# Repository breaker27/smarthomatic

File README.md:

smarthomatic
============

smarthomatic (SHC) is an **open source home automation system**
providing a framework for building up a bigger network of sensors and
actuators that all work together. It consists of several completely
developed hardware devices you can build up yourself and the software
running on those devices.

This project **concentrates on the hardware devices** and their software
(firmware), not on end user interfaces for control tasks like web
interfaces or smartphone apps. Nonetheless this system is designed to be
easily integrated in such systems.

For more information, visit the website at
http://www.smarthomatic.org.

License Information Hardware Files
----------------------------------

All **hardware** files (schematics and layout) are stored under the
"hardware" subdirectory and are copyright (c) 2013 Uwe Freese, licensed
under the Creative Commons Attribution-ShareAlike 3.0 Unported:
(CC BY-SA 3.0): http://creativecommons.org/licenses/by-sa/3.0/deed.en.

License Information Software
----------------------------

All files not in the hardware subdirectory belong to the software (device
firmware, control software or tools).

The smarthomatic **software** is free software: you can redistribute
it and/or modify it under the terms of the GNU General Public License as
published by the Free Software Foundation, either version 3 of the
License, or (at your option) any later version.

smarthomatic is distributed in the hope that it will be useful, but
WITHOUT ANY WARRANTY; without even the implied warranty of
MERCHANTABILITY or FITNESS FOR A PARTICULAR PURPOSE. See the GNU General
Public License for more details.

You should have received a copy of the GNU General Public License along
with smarthomatic. If not, see <http://www.gnu.org/licenses/>.

License Information Logo
------------------------

The smarthomatic logo ("House") and logotype, also used in the hardware
layouts, are copyrighted (c) by 2013 by Uwe Freese.

The logo and logotype may be used on hardware (boards or devices) or
description of those only for private purposes for devices included in
the project repository and which are therefore available to the public.
For derived or modified versions, devices not existing in the repository,
completely different products or for commercial boards or devices or to
describe them, the logo must not be used without explicit permission from
Uwe Freese.

For more information on using the logo or logotype outside the hardware
layouts, please read the legal info on the website
http://www.smarthomatic.org.

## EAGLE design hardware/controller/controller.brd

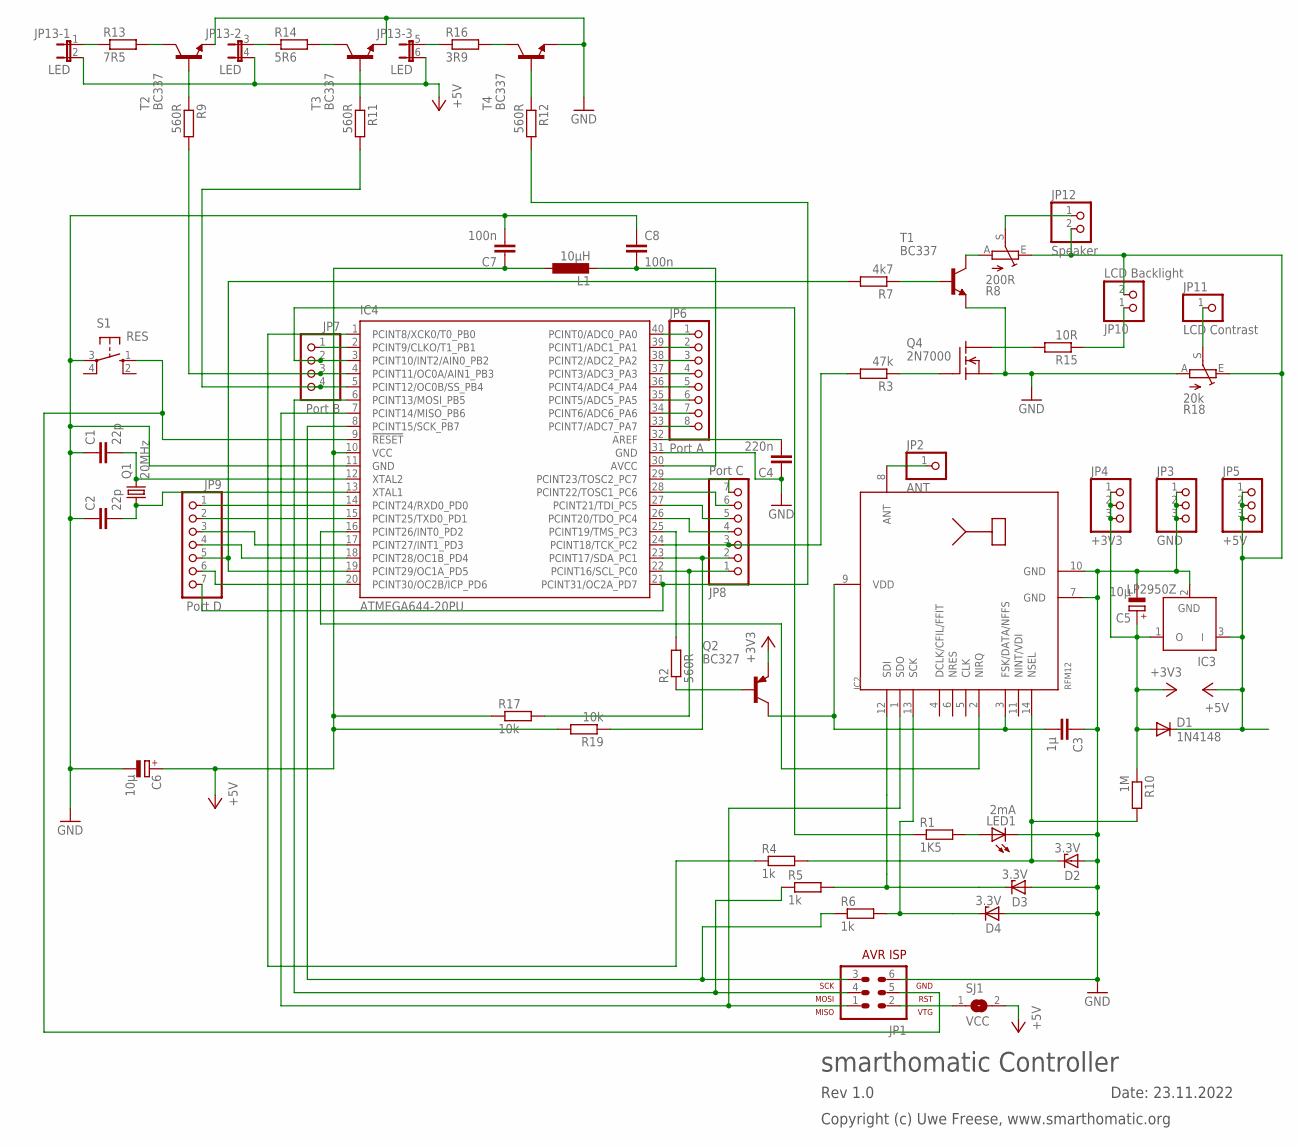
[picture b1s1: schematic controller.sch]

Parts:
C1, C2: 22p; C025-024X044
C3: 1µ; C025-030X050
C4: 220n; C025-030X050
C5, C6: 10µ; E1,8-4
C7, C8: 100n; C050-024X044
D1: 1N4148; DO35-7
D2, D3, D4: 3.3V; ZDIO-5
IC2: RFM12; RFM
IC3: LP2950Z; TO92
IC4: ATMEGA644-20PU; DIL40
JP1: AVR-ISP-6
JP2: ANT; 1X01
JP3: GND; 1X03
JP4: +3V3; 1X03
JP5: +5V; 1X03
JP6: Port A; 1X08
JP7: Port B; 1X04
JP8: Port C; 1X07
JP9: Port D; 1X07
JP10: LCD Backlight; 1X02
JP11: LCD Contrast; 1X01
JP12: Speaker; 1X02
JP13: LED; JP3Q
L1: 10µH; 0207/10
LED1: 2mA; LED3MM
Q1: 20MHz; HC49/S
Q2: BC327; TO92
Q4: 2N7000; TO-92
R1: 1K5; 0207/7
R2, R9, R11, R12: 560R; 0207/7
R3: 47k; 0207/7
R4, R5, R6: 1k; 0207/7
R7: 4k7; 0207/7
R8: 200R; CA9H
R10: 1M; 0207/7
R13: 7R5; 0207/7
R14: 5R6; 0207/7
R15: 10R; 0207/7
R16: 3R9; 0207/7
R17, R19: 10k; 0207/7
R18: 20k; CA9H
S1: RES; B3F-10XX
SJ1: VCC; SJ
T1, T2, T3, T4: BC337; TO92

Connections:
+3V3: C5.+, D1.A, IC3.1 (O), JP4.1, JP4.2, JP4.3, Q2.1 (E), R10.1
+5V: C6.+, C7.1, D1.C, IC3.3 (I), IC4.10 (VCC), JP5.1, JP5.2, JP5.3, JP10.2, JP12.2, JP13.2, JP13.4 (2), JP13.6 (2), L1.1, R8.E, R17.1, R18.E, R19.2, SJ1.2
GND: C1.1, C2.1, C3.1, C4.1, C5.-, C6.-, C7.2, C8.1, D2.A, D3.A, D4.A, IC2.7 (GND), IC2.10 (GND), IC3.2 (GND), IC4.11 (GND), IC4.31 (GND), JP1.6, JP3.1, JP3.2, JP3.3, LED1.K (C), Q4.1 (S), R18.A, S1.3, T1.1 (E), T2.1 (E), T3.1 (E), T4.1 (E)
unnamed: C1.2, IC4.12 (XTAL2), Q1.2
unnamed: C2.2, IC4.13 (XTAL1), Q1.1
unnamed: IC4.6 (PCINT13/MOSI_PB5), JP1.4, R5.1
unnamed: IC2.1 (SDO), IC4.7 (PCINT14/MISO_PB6), JP1.1
unnamed: D4.C, IC2.13 (SCK), R6.2
unnamed: C4.2, IC4.32 (AREF)
unnamed: IC4.8 (PCINT15/SCK_PB7), JP1.3, R6.1
unnamed: IC4.9 (!RESET), JP1.5, S1.1 (S)
unnamed: IC4.2 (PCINT9/CLKO/T1_PB1), JP7.1
unnamed: IC4.40 (PCINT0/ADC0_PA0), JP6.1
unnamed: IC4.39 (PCINT1/ADC1_PA1), JP6.2
unnamed: LED1.A, R1.2
unnamed: IC4.26 (PCINT20/TDO_PC4), JP8.4
unnamed: IC4.38 (PCINT2/ADC2_PA2), JP6.3
unnamed: IC2.2 (NIRQ), IC4.16 (PCINT26/INT0_PD2)
unnamed: D3.C, IC2.12 (SDI), R5.2
unnamed: IC4.37 (PCINT3/ADC3_PA3), JP6.4
unnamed: JP1.2, SJ1.1
unnamed: IC4.36 (PCINT4/ADC4_PA4), JP6.5
unnamed: IC4.35 (PCINT5/ADC5_PA5), JP6.6
unnamed: IC4.29 (PCINT23/TOSC2_PC7), JP8.7
unnamed: IC4.34 (PCINT6/ADC6_PA6), JP6.7
unnamed: IC4.33 (PCINT7/ADC7_PA7), JP6.8
unnamed: IC4.3 (PCINT10/INT2/AIN0_PB2), JP7.2, R1.1
unnamed: IC2.8 (ANT), JP2.1
unnamed: IC4.1 (PCINT8/XCK0/T0_PB0), R4.1
unnamed: D2.C, IC2.14 (NSEL), R4.2, R10.2
unnamed: IC4.25 (PCINT19/TMS_PC3), R2.2
unnamed: Q2.2 (B), R2.1
unnamed: IC4.4 (PCINT11/OC0A/AIN1_PB3), JP7.3, R9.2
unnamed: IC4.5 (PCINT12/OC0B/SS_PB4), JP7.4, R11.2
unnamed: C3.2, IC2.3 (FSK/DATA/NFFS), IC2.9 (VDD), Q2.3 (C)
unnamed: IC4.22 (PCINT16/SCL_PC0), JP8.1, R17.2
unnamed: IC4.23 (PCINT17/SDA_PC1), JP8.2, R19.1
unnamed: IC4.24 (PCINT18/TCK_PC2), JP8.3, R3.2
unnamed: IC4.19 (PCINT29/OC1A_PD5), JP9.5, R7.2
unnamed: IC4.28 (PCINT22/TOSC1_PC6), JP8.6
unnamed: IC4.20 (PCINT30/OC2B/ICP_PD6), JP9.6
unnamed: IC4.14 (PCINT24/RXD0_PD0), JP9.1
unnamed: IC4.15 (PCINT25/TXD0_PD1), JP9.2
unnamed: IC4.17 (PCINT27/INT1_PD3), JP9.3
unnamed: IC4.18 (PCINT28/OC1B_PD4), JP9.4
unnamed: IC4.21 (PCINT31/OC2A_PD7), JP9.7, R12.2
unnamed: IC4.27 (PCINT21/TDI_PC5), JP8.5
unnamed: C8.2, IC4.30 (AVCC), L1.2
unnamed: R7.1, T1.2 (B)
unnamed: R8.A, T1.3 (C)
unnamed: JP12.1, R8.S
unnamed: Q4.2 (G), R3.1
unnamed: Q4.3 (D), R15.2
unnamed: JP10.1, R15.1
unnamed: JP11.1, R18.S
unnamed: R9.1, T2.2 (B)
unnamed: R11.1, T3.2 (B)
unnamed: R12.1, T4.2 (B)
unnamed: JP13.1, R13.1
unnamed: R13.2, T2.3 (C)
unnamed: JP13.3 (1), R14.1
unnamed: R14.2, T3.3 (C)
unnamed: JP13.5 (1), R16.1
unnamed: R16.2, T4.3 (C)

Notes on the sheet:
smarthomatic Controller
Date: 23.11.2022
Rev 1.0
Copyright (c) Uwe Freese, www.smarthomatic.org

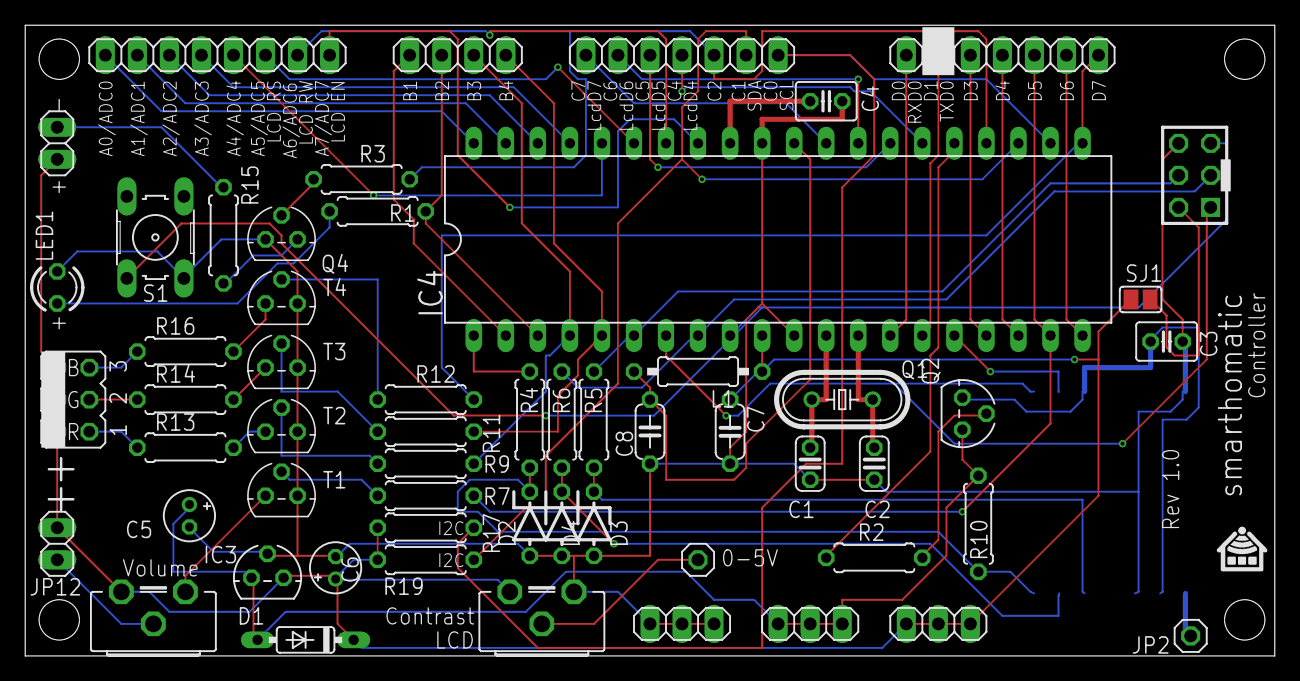
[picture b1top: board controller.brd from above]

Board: 2 copper layers, 99.1 x 50.0 mm, 58 parts (1 on the bottom side), 64 nets.

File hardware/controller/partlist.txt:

Partlist

Exported from controller.sch at 24.11.2022 18:18:30

EAGLE Version 7.1.0 Copyright (c) 1988-2014 CadSoft

Assembly variant: 

Part     Value          Device          Package      Library        Sheet

C1       22p            C-EU025-024X044 C025-024X044 rcl            1
C2       22p            C-EU025-024X044 C025-024X044 rcl            1
C3       1µ             C-EU025-030X050 C025-030X050 rcl            1
C4       220n           C-EU025-030X050 C025-030X050 rcl            1
C5       10µ            CPOL-EUE1.8-4   E1,8-4       rcl            1
C6       10µ            CPOL-EUE1.8-4   E1,8-4       rcl            1
C7       100n           C-EU050-024X044 C050-024X044 rcl            1
C8       100n           C-EU050-024X044 C050-024X044 rcl            1
D1       1N4148         1N4148DO35-7    DO35-7       diode          1
D2       3.3V           ZENER-DIODEZD-5 ZDIO-5       diode          1
D3       3.3V           ZENER-DIODEZD-5 ZDIO-5       diode          1
D4       3.3V           ZENER-DIODEZD-5 ZDIO-5       diode          1
IC2      RFM12          RFM12           RFM          hopeRF         1
IC3      LP2950Z        LP2950Z         TO92         linear         1
IC4      ATMEGA644-20PU ATMEGA644-20PU  DIL40        atmel          1
JP1      AVR-ISP-6      AVR-ISP-6       AVR-ISP-6    avr-5-4.16     1
JP2      ANT            PINHD-1X1       1X01         pinhead        1
JP3      GND            PINHD-1X3       1X03         pinhead        1
JP4      +3V3           PINHD-1X3       1X03         pinhead        1
JP5      +5V            PINHD-1X3       1X03         pinhead        1
JP6      Port A         PINHD-1X8       1X08         pinhead        1
JP7      Port B         PINHD-1X4       1X04         pinhead        1
JP8      Port C         PINHD-1X7       1X07         pinhead        1
JP9      Port D         PINHD-1X7       1X07         pinhead        1
JP10     LCD Backlight  PINHD-1X2       1X02         pinhead        1
JP11     LCD Contrast   PINHD-1X1       1X01         pinhead        1
JP12     Speaker        PINHD-1X2       1X02         pinhead        1
JP13     LED            JP3QE           JP3Q         jumper         1
L1       10µH           L-EU0207/10     0207/10      rcl            1
LED1     2mA            LED3MM          LED3MM       led            1
Q1       20MHz          CRYSTALHC49S    HC49/S       crystal        1
Q2       BC327          BC327           TO92         transistor-pnp 1
Q4       2N7000         TN0602N3        TO-92        transistor-fet 1
R1       1K5            R-EU_0207/7     0207/7       rcl            1
R2       560R           R-EU_0207/7     0207/7       rcl            1
R3       47k            R-EU_0207/7     0207/7       rcl            1
R4       1k             R-EU_0207/7     0207/7       rcl            1
R5       1k             R-EU_0207/7     0207/7       rcl            1
R6       1k             R-EU_0207/7     0207/7       rcl            1
R7       4k7            R-EU_0207/7     0207/7       rcl            1
R8       200R           TRIM_EU-CA9H    CA9H         pot            1
R9       560R           R-EU_0207/7     0207/7       rcl            1
R10      1M             R-EU_0207/7     0207/7       rcl            1
R11      560R           R-EU_0207/7     0207/7       rcl            1
R12      560R           R-EU_0207/7     0207/7       rcl            1
R13      7R5            R-EU_0207/7     0207/7       rcl            1
R14      5R6            R-EU_0207/7     0207/7       rcl            1
R15      10R            R-EU_0207/7     0207/7       rcl            1
R16      3R9            R-EU_0207/7     0207/7       rcl            1
R17      10k            R-EU_0207/7     0207/7       rcl            1
R18      20k            TRIM_EU-CA9H    CA9H         pot            1
R19      10k            R-EU_0207/7     0207/7       rcl            1
S1       RES            10-XX           B3F-10XX     switch-omron   1
SJ1      VCC            SJ              SJ           jumper         1
T1       BC337          BC337           TO92         transistor     1
T2       BC337          BC337           TO92         transistor     1
T3       BC337          BC337           TO92         transistor     1
T4       BC337          BC337           TO92         transistor     1

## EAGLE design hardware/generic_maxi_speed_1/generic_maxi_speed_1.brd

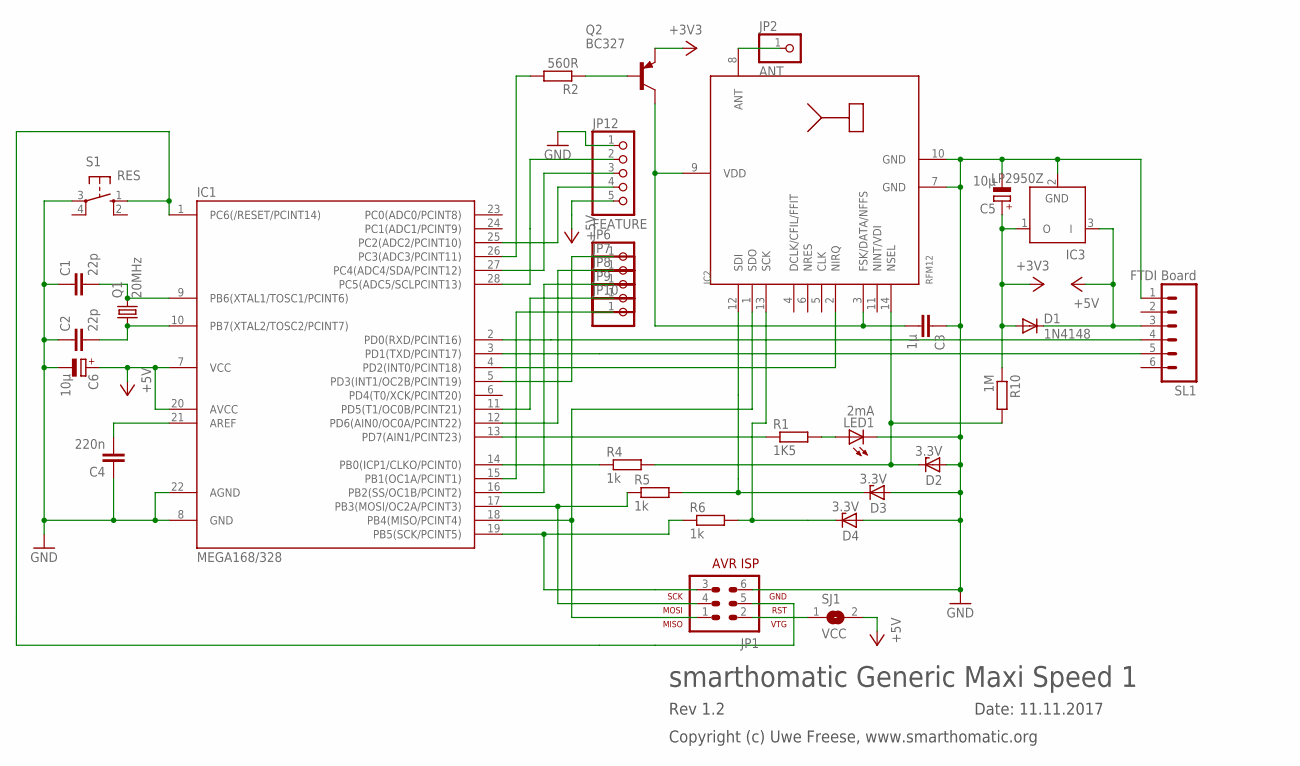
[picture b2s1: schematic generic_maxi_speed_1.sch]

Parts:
C1, C2: 22p; C025-024X044
C3: 1µ; C025-030X050
C4: 220n; C025-030X050
C5, C6: 10µ; E1,8-4
D1: 1N4148; DO35-7
D2, D3, D4: 3.3V; ZDIO-5
IC1: MEGA168/328; DIL28-3
IC2: RFM12; RFM
IC3: LP2950Z; TO92
JP1: AVR-ISP-6
JP2: ANT; 1X01
JP6, JP7, JP8, JP9, JP10: PINHD-1X1; 1X01
JP12: FEATURE; 1X05
LED1: 2mA; LED3MM
Q1: 20MHz; HC49/S
Q2: BC327; TO92
R1: 1K5; 0207/7
R2: 560R; 0207/7
R4, R5, R6: 1k; 0207/7
R10: 1M; 0207/7
S1: RES; B3F-10XX
SJ1: VCC; SJ
SL1: FTDI Board; 06P

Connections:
+3V3: C5.+, D1.A, IC3.1 (O), Q2.1 (E), R10.1
+5V: C6.+, D1.C, IC1.7 (VCC), IC1.20 (AVCC), IC3.3 (I), JP12.5, SJ1.2, SL1.3
GND: C1.1, C2.1, C3.1, C4.1, C5.-, C6.-, D2.A, D3.A, D4.A, IC1.8 (GND), IC1.22 (AGND), IC2.7 (GND), IC2.10 (GND), IC3.2 (GND), JP1.6, JP12.1, LED1.K (C), S1.3, SL1.1
unnamed: C1.2, IC1.9 (PB6(XTAL1/TOSC1/PCINT6)), Q1.2
unnamed: C2.2, IC1.10 (PB7(XTAL2/TOSC2/PCINT7)), Q1.1
unnamed: IC1.17 (PB3(MOSI/OC2A/PCINT3)), JP1.4, R5.1
unnamed: IC1.18 (PB4(MISO/PCINT4)), IC2.1 (SDO), JP1.1
unnamed: D4.C, IC2.13 (SCK), R6.2
unnamed: IC1.28 (PC5(ADC5/SCLPCINT13)), JP12.2
unnamed: IC1.19 (PB5(SCK/PCINT5)), JP1.3, R6.1
unnamed: IC1.1 (PC6(/RESET/PCINT14)), JP1.5, S1.1 (S)
unnamed: IC1.3 (PD1(TXD/PCINT17)), SL1.5
unnamed: IC1.2 (PD0(RXD/PCINT16)), SL1.4
unnamed: IC1.27 (PC4(ADC4/SDA/PCINT12)), JP12.3
unnamed: LED1.A, R1.2
unnamed: IC1.25 (PC2(ADC2/PCINT10)), JP12.4
unnamed: IC1.4 (PD2(INT0/PCINT18)), IC2.2 (NIRQ)
unnamed: D3.C, IC2.12 (SDI), R5.2
unnamed: IC1.5 (PD3(INT1/OC2B/PCINT19)), JP6.1
unnamed: JP1.2, SJ1.1
unnamed: IC1.11 (PD5(T1/OC0B/PCINT21)), JP9.1
unnamed: IC1.12 (PD6(AIN0/OC0A/PCINT22)), JP7.1
unnamed: IC1.13 (PD7(AIN1/PCINT23)), R1.1
unnamed: IC1.15 (PB1(OC1A/PCINT1)), JP10.1
unnamed: IC1.16 (PB2(SS/OC1B/PCINT2)), JP8.1
unnamed: C4.2, IC1.21 (AREF)
unnamed: IC2.8 (ANT), JP2.1
unnamed: IC1.14 (PB0(ICP1/CLKO/PCINT0)), R4.1
unnamed: D2.C, IC2.14 (NSEL), R4.2, R10.2
unnamed: IC1.26 (PC3(ADC3/PCINT11)), R2.2
unnamed: Q2.2 (B), R2.1
unnamed: C3.2, IC2.3 (FSK/DATA/NFFS), IC2.9 (VDD), Q2.3 (C)

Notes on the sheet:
smarthomatic Generic Maxi Speed 1
Date: 11.11.2017
Rev 1.2
Copyright (c) Uwe Freese, www.smarthomatic.org

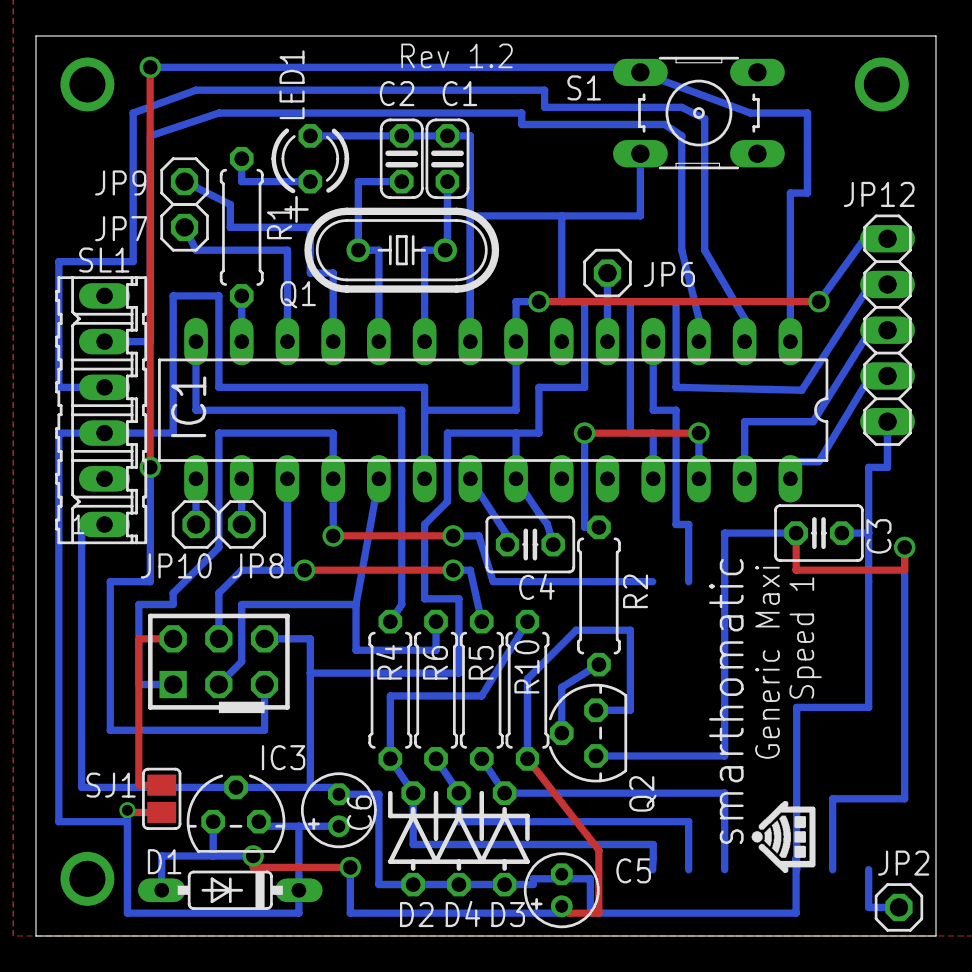
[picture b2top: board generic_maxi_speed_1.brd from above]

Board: 2 copper layers, 50.0 x 50.0 mm, 33 parts (1 on the bottom side), 32 nets.

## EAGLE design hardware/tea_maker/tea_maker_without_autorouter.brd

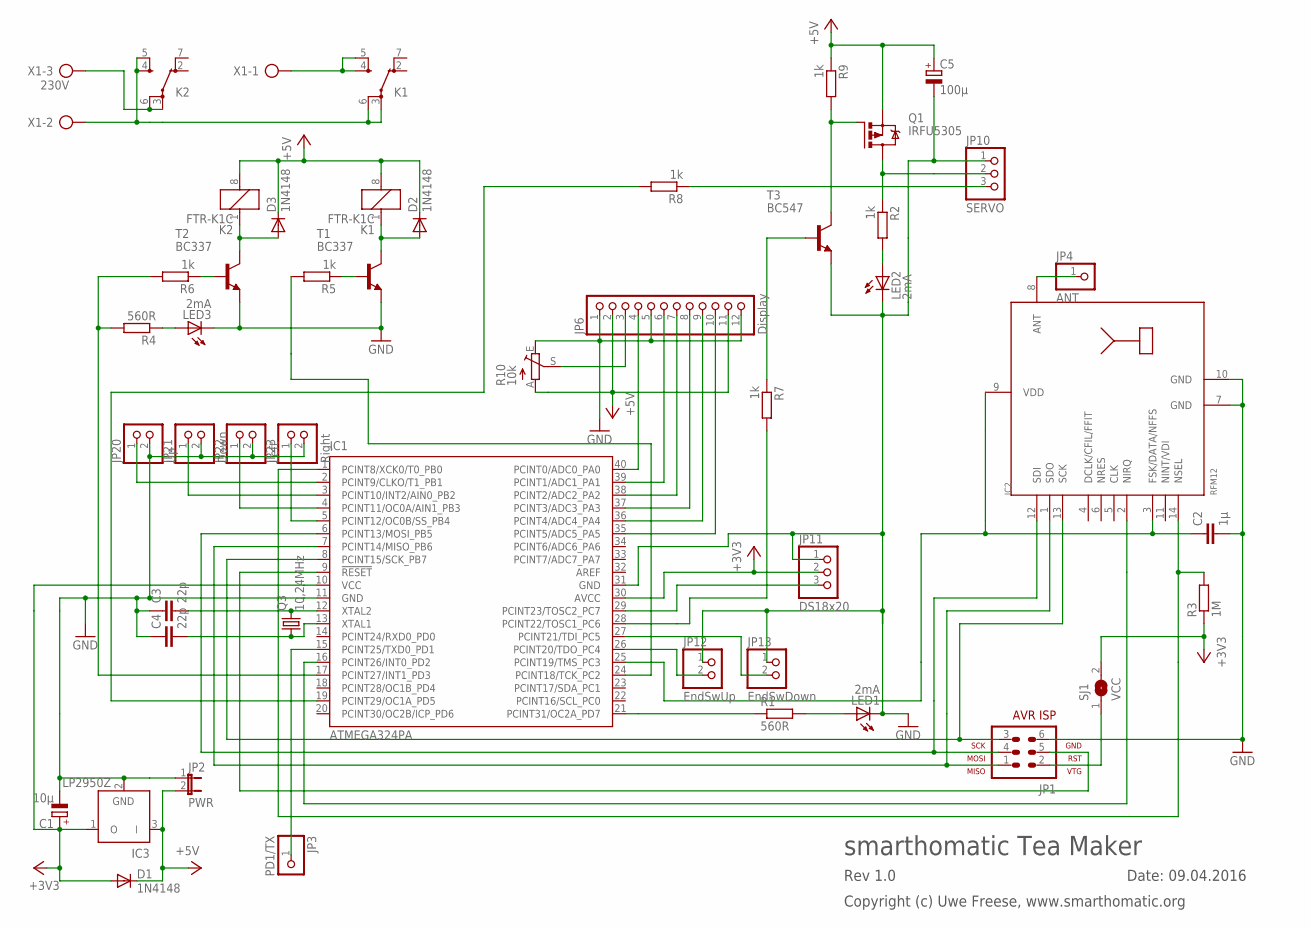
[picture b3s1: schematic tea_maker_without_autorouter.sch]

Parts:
C1: 10µ; E1,8-4
C2: 1µ; C5B3.5
C3, C4: 22p; C025-024X044
C5: 100µ; E2,5-7
D1, D2, D3: 1N4148; DO35-7
IC1: ATMEGA324PA; DIL40
IC2: RFM12; RFM
IC3: LP2950Z; TO92
JP1: AVR-ISP-6
JP2: PWR; JP1
JP3: PD1/TX; 1X01
JP4: ANT; 1X01
JP6: Display; 1X12
JP10: SERVO; 1X03
JP11: DS18x20; 1X03
JP12: EndSwUp; 1X02
JP13: EndSwDown; 1X02
JP20: Up; 1X02
JP21: Down; 1X02
JP22: Left; 1X02
JP23: Right; 1X02
K1, K2: FTR-K1C
LED1, LED2, LED3: 2mA; LED3MM
Q1: IRFU5305; I-PAK_TO251AA
Q3: 10,24MHz; HC49/S
R1, R4: 560R; 0207/7
R2, R5, R6, R7, R8, R9: 1k; 0207/7
R3: 1M; 0207/7
R10: 10k; PT-10S
SJ1: VCC; SJ
T1, T2: BC337; TO92
T3: BC547; TO92
X1: 230V; AK500/3

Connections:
+3V3: C1.+, D1.A, IC1.10 (VCC), IC1.30 (AVCC), IC3.1 (O), JP11.2, R3.1, SJ1.2
+5V: C5.+, D1.C, D2.C, D3.C, IC3.3 (I), JP2.2, JP6.2, JP6.11, K1.8 (2), K2.8 (2), Q1.3 (S), R9.1, R10.A
GND: C1.-, C2.2, C3.1, C4.1, C5.-, IC1.11 (GND), IC1.31 (GND), IC2.7 (GND), IC2.10 (GND), IC3.2 (GND), JP1.6, JP2.1, JP6.1, JP6.5, JP6.12, JP10.1, JP11.1, JP12.1, JP13.1, JP20.2, JP21.2, JP22.2, JP23.2, LED1.K (C), LED2.K (C), LED3.K (C), R10.E, T1.1 (E), T2.1 (E), T3.1 (E)
unnamed: IC1.2 (PCINT9/CLKO/T1_PB1), JP20.1
unnamed: JP1.2, SJ1.1
unnamed: IC1.6 (PCINT13/MOSI_PB5), IC2.12 (SDI), JP1.4
unnamed: IC1.7 (PCINT14/MISO_PB6), IC2.1 (SDO), JP1.1
unnamed: IC1.8 (PCINT15/SCK_PB7), IC2.13 (SCK), JP1.3
unnamed: IC1.21 (PCINT31/OC2A_PD7), R1.1
unnamed: R5.1, T1.2 (B)
unnamed: IC1.9 (!RESET), JP1.5
unnamed: D2.A, K1.1, T1.3 (C)
unnamed: IC1.3 (PCINT10/INT2/AIN0_PB2), JP21.1
unnamed: IC2.8 (ANT), JP4.1
unnamed: LED1.A, R1.2
unnamed: IC1.1 (PCINT8/XCK0/T0_PB0), IC2.14 (NSEL), R3.2
unnamed: LED3.A, R4.1
unnamed: IC1.16 (PCINT26/INT0_PD2), IC2.2 (NIRQ)
unnamed: IC1.4 (PCINT11/OC0A/AIN1_PB3), JP22.1
unnamed: IC1.5 (PCINT12/OC0B/SS_PB4), JP23.1
unnamed: K1.4 (SA), K1.5 (SB), X1.1
unnamed: IC1.40 (PCINT0/ADC0_PA0), JP6.4
unnamed: IC1.15 (PCINT25/TXD0_PD1), JP3.1
unnamed: K2.3 (PA), K2.6 (PB), X1.3
unnamed: C2.1, IC1.25 (PCINT19/TMS_PC3), IC2.3 (FSK/DATA/NFFS), IC2.9 (VDD)
unnamed: IC1.39 (PCINT1/ADC1_PA1), JP6.6
unnamed: IC1.24 (PCINT18/TCK_PC2), R5.2
unnamed: R6.1, T2.2 (B)
unnamed: IC1.38 (PCINT2/ADC2_PA2), JP6.7
unnamed: IC1.37 (PCINT3/ADC3_PA3), JP6.8
unnamed: IC1.36 (PCINT4/ADC4_PA4), JP6.9
unnamed: IC1.35 (PCINT5/ADC5_PA5), JP6.10
unnamed: LED2.A, R2.2
unnamed: IC1.28 (PCINT22/TOSC1_PC6), R7.2
unnamed: JP6.3, R10.S
unnamed: R7.1, T3.2 (B)
unnamed: Q1.1 (G), R9.2, T3.3 (C)
unnamed: JP10.2, Q1.2 (D), R2.1
unnamed: K1.3 (PA), K1.6 (PB), K2.4 (SA), K2.5 (SB), X1.2
unnamed: JP10.3, R8.1
unnamed: IC1.19 (PCINT29/OC1A_PD5), R8.2
unnamed: C3.2, IC1.12 (XTAL2), Q3.2
unnamed: C4.2, IC1.13 (XTAL1), Q3.1
unnamed: IC1.29 (PCINT23/TOSC2_PC7), JP11.3
unnamed: D3.A, K2.1, T2.3 (C)
unnamed: IC1.26 (PCINT20/TDO_PC4), JP12.2
unnamed: IC1.17 (PCINT27/INT1_PD3), R4.2, R6.2
unnamed: IC1.27 (PCINT21/TDI_PC5), JP13.2

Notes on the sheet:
smarthomatic Tea Maker
Date: 09.04.2016
Rev 1.0
Copyright (c) Uwe Freese, www.smarthomatic.org

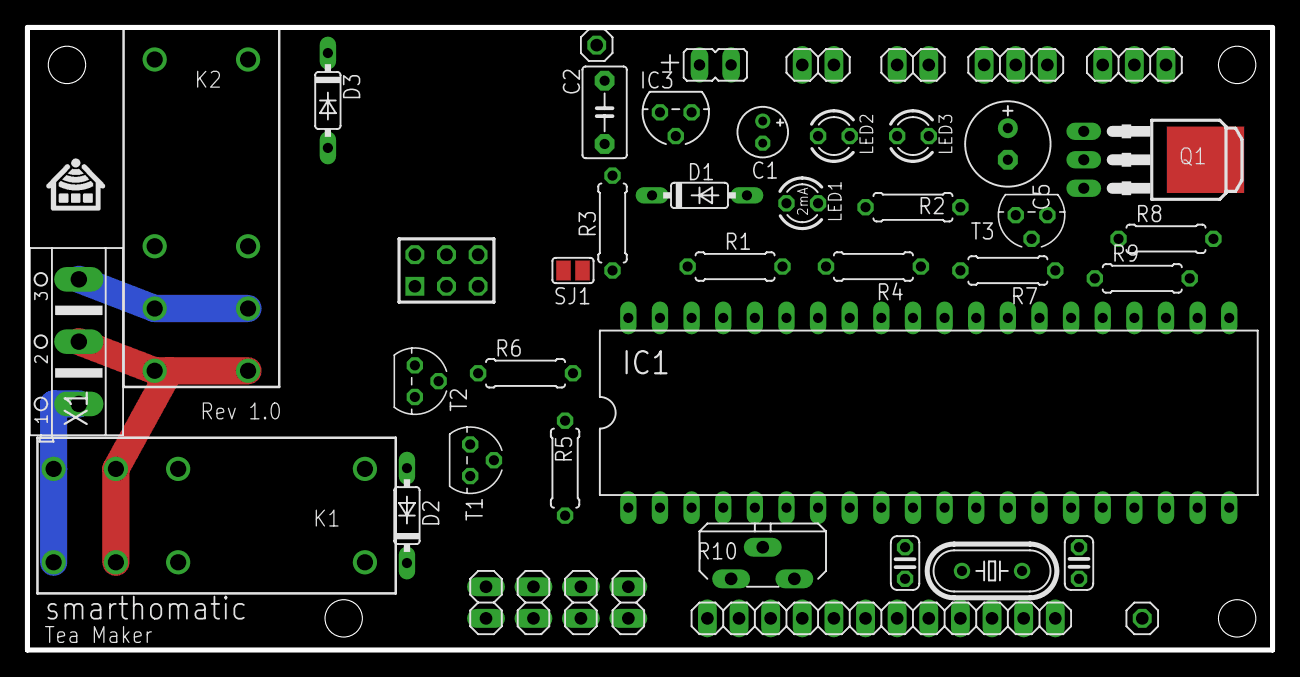
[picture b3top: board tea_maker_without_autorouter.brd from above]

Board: 2 copper layers, 100.0 x 50.0 mm, 46 parts (1 on the bottom side), 48 nets.

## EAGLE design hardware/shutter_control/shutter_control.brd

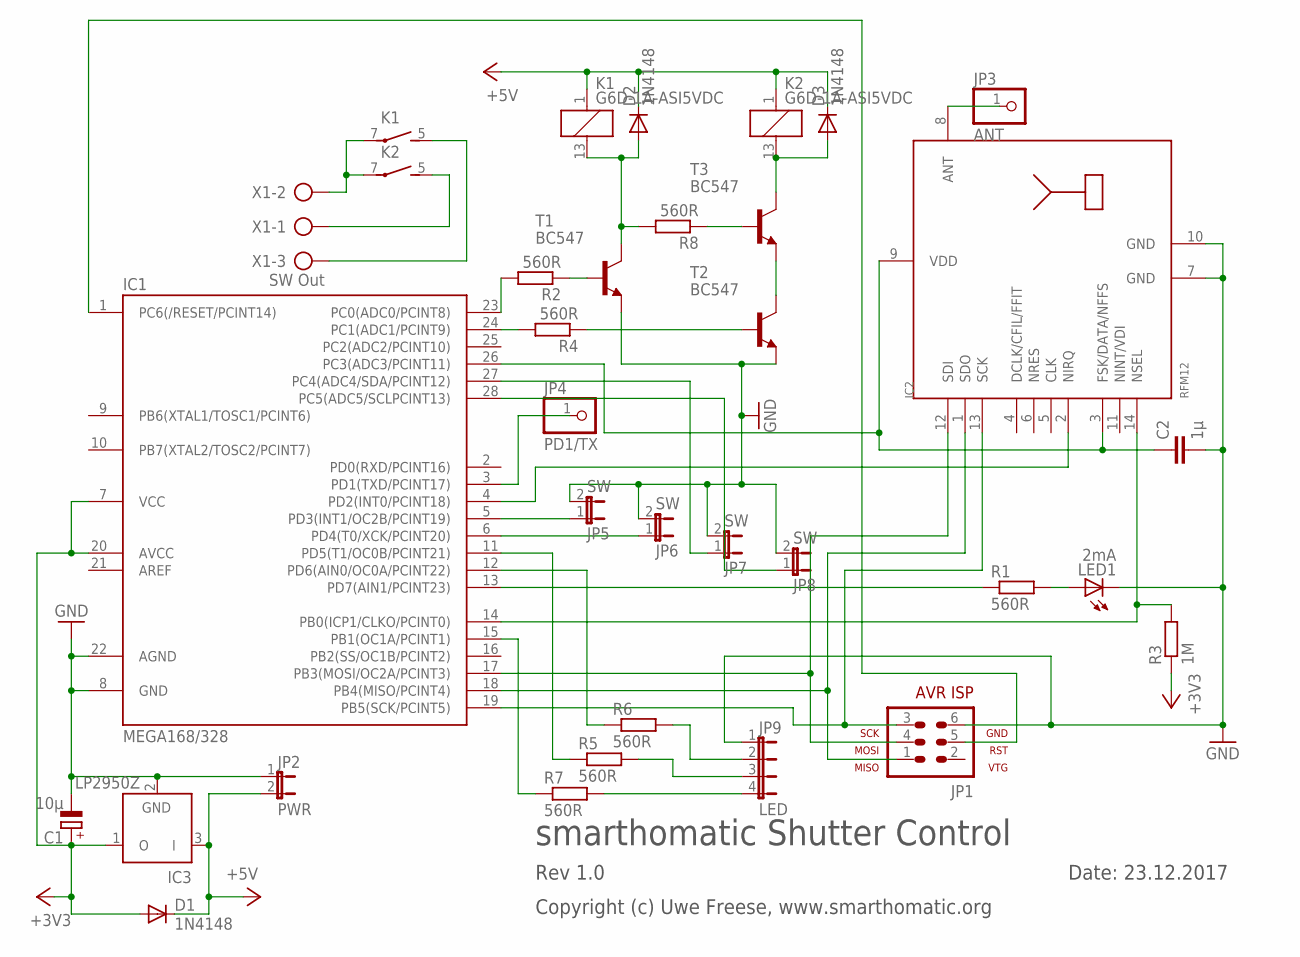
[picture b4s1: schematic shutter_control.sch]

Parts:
C1: 10µ; E1,8-4
C2: 1µ; C5B3.5
D1, D2, D3: 1N4148; DO35-7
IC1: MEGA168/328; DIL28-3
IC2: RFM12; RFM
IC3: LP2950Z; TO92
JP1: AVR-ISP-6
JP2: PWR; JP1
JP3: ANT; 1X01
JP4: PD1/TX; 1X01
JP5, JP6, JP7, JP8: SW; JP1
JP9: LED; JP4
K1, K2: G6D-1A-ASI5VDC; G6D
LED1: 2mA; LED3MM
R1, R2, R4, R5, R6, R7, R8: 560R; 0207/7
R3: 1M; 0207/7
T1, T2, T3: BC547; TO92
X1: SW Out; AK500/3

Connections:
+3V3: C1.+, D1.A, IC1.7 (VCC), IC1.20 (AVCC), IC3.1 (O), R3.1
+5V: D1.C, D2.C, D3.C, IC3.3 (I), JP2.2, K1.1, K2.1
GND: C1.-, C2.2, IC1.8 (GND), IC1.22 (AGND), IC2.7 (GND), IC2.10 (GND), IC3.2 (GND), JP1.6, JP2.1, JP5.2, JP6.2, JP7.2, JP8.2, JP9.1, LED1.K (C), T1.1 (E), T2.1 (E)
unnamed: IC1.23 (PC0(ADC0/PCINT8)), R2.2
unnamed: IC1.17 (PB3(MOSI/OC2A/PCINT3)), IC2.12 (SDI), JP1.4
unnamed: IC1.18 (PB4(MISO/PCINT4)), IC2.1 (SDO), JP1.1
unnamed: IC1.19 (PB5(SCK/PCINT5)), IC2.13 (SCK), JP1.3
unnamed: IC1.13 (PD7(AIN1/PCINT23)), R1.1
unnamed: R2.1, T1.2 (B)
unnamed: IC1.1 (PC6(/RESET/PCINT14)), JP1.5
unnamed: IC1.6 (PD4(T0/XCK/PCINT20)), JP6.1
unnamed: IC1.5 (PD3(INT1/OC2B/PCINT19)), JP5.1
unnamed: IC2.8 (ANT), JP3.1
unnamed: LED1.A, R1.2
unnamed: IC1.14 (PB0(ICP1/CLKO/PCINT0)), IC2.14 (NSEL), R3.2
unnamed: IC1.24 (PC1(ADC1/PCINT9)), R4.2
unnamed: IC1.4 (PD2(INT0/PCINT18)), IC2.2 (NIRQ)
unnamed: K1.7, K2.7, X1.2
unnamed: R4.1, T2.2 (B)
unnamed: D2.A, K1.13 (2), R8.2, T1.3 (C)
unnamed: D3.A, K2.13 (2), T3.3 (C)
unnamed: IC1.3 (PD1(TXD/PCINT17)), JP4.1
unnamed: IC1.12 (PD6(AIN0/OC0A/PCINT22)), R6.1
unnamed: C2.1, IC1.26 (PC3(ADC3/PCINT11)), IC2.3 (FSK/DATA/NFFS), IC2.9 (VDD)
unnamed: IC1.11 (PD5(T1/OC0B/PCINT21)), R5.1
unnamed: IC1.15 (PB1(OC1A/PCINT1)), R7.1
unnamed: JP9.4, R7.2
unnamed: JP9.3, R5.2
unnamed: JP9.2, R6.2
unnamed: IC1.27 (PC4(ADC4/SDA/PCINT12)), JP7.1
unnamed: K1.5 (S), X1.3
unnamed: K2.5 (S), X1.1
unnamed: IC1.28 (PC5(ADC5/SCLPCINT13)), JP8.1
unnamed: T2.3 (C), T3.1 (E)
unnamed: R8.1, T3.2 (B)

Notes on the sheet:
smarthomatic Shutter Control
Date: 23.12.2017
Rev 1.0
Copyright (c) Uwe Freese, www.smarthomatic.org

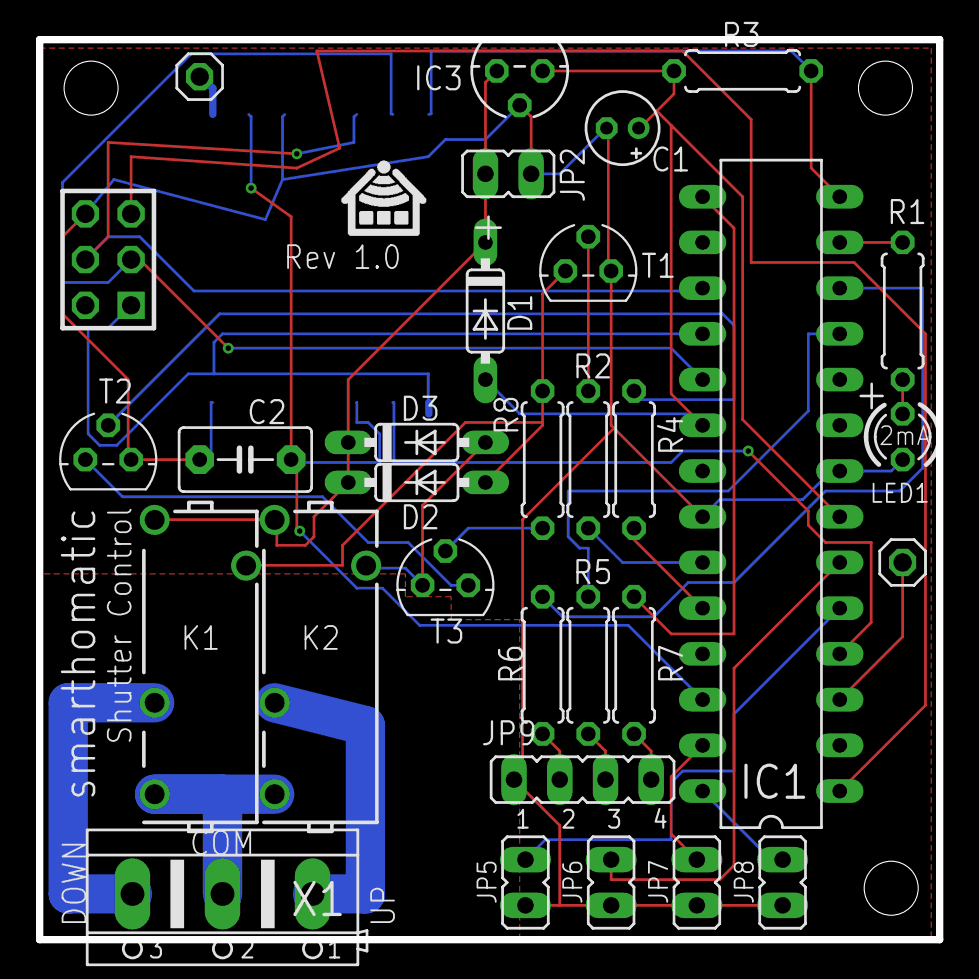
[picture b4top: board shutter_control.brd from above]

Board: 2 copper layers, 50.0 x 50.0 mm, 32 parts (1 on the bottom side), 35 nets.

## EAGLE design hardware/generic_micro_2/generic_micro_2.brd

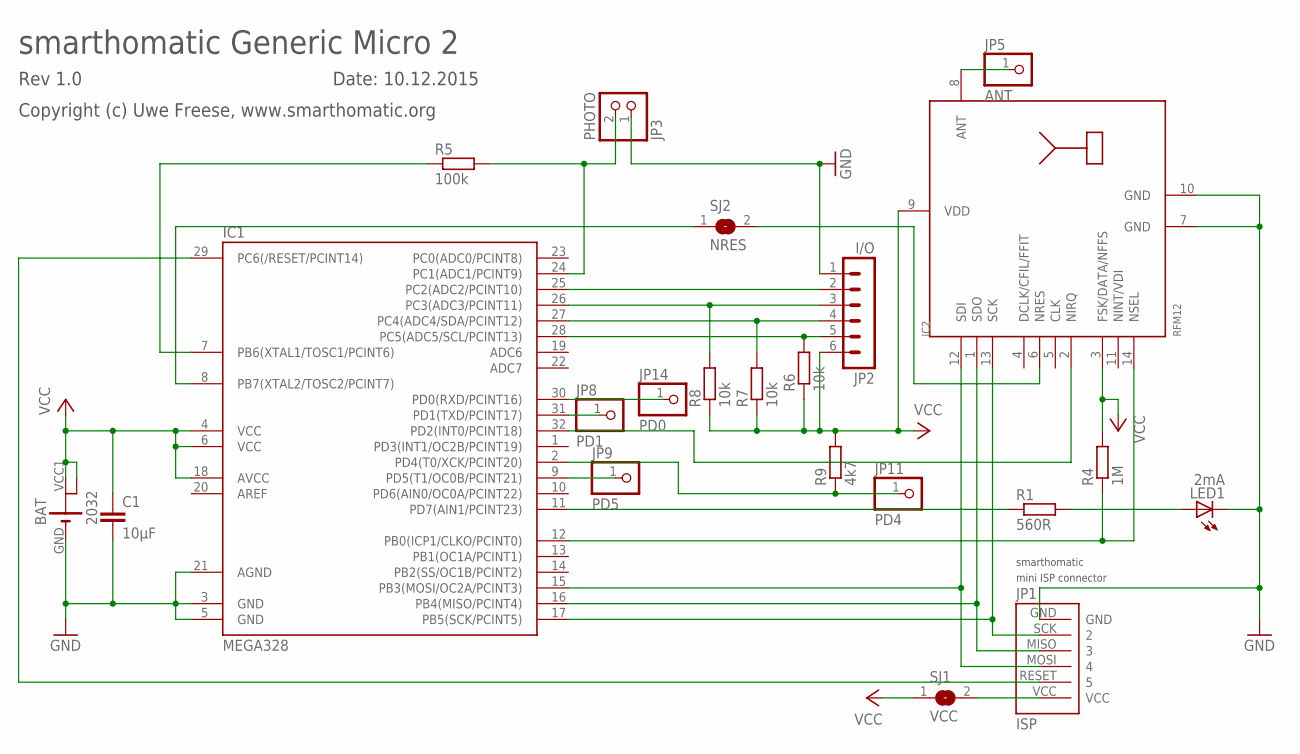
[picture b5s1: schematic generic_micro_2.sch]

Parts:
BAT: 2032; KZH20SMD
C1: 10µF; C0603
IC1: MEGA328; TQFP32-08
IC2: RFM12; RFM
JP1: ISP; PINHD_1X6_1.27
JP2: I/O; MA06-1
JP3: PHOTO; 1X02
JP5: ANT; 1X01
JP8: PD1; 1X01
JP9: PD5; 1X01
JP11: PD4; 1X01
JP14: PD0; 1X01
LED1: 2mA; LED3MM
R1: 560R; R0603
R4: 1M; R0603
R5: 100k; R0603
R6, R7, R8: 10k; R0603
R9: 4k7; R0603
SJ1: VCC; SJ
SJ2: NRES; SJ

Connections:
GND: BAT.GND, C1.2, IC1.3 (GND), IC1.5 (GND), IC1.21 (AGND), IC2.7 (GND), IC2.10 (GND), JP1.GND, JP2.1, JP3.1, LED1.K (C)
unnamed: JP1.VCC, SJ1.2
unnamed: IC1.26 (PC3(ADC3/PCINT11)), JP2.3, R8.2
unnamed: IC1.15 (PB3(MOSI/OC2A/PCINT3)), IC2.12 (SDI), JP1.MOSI (4)
unnamed: IC1.16 (PB4(MISO/PCINT4)), IC2.1 (SDO), JP1.MISO (3)
unnamed: IC1.17 (PB5(SCK/PCINT5)), IC2.13 (SCK), JP1.SCK (2)
unnamed: IC1.11 (PD7(AIN1/PCINT23)), R1.1
unnamed: IC1.27 (PC4(ADC4/SDA/PCINT12)), JP2.4, R7.2
unnamed: IC1.29 (PC6(/RESET/PCINT14)), JP1.RESET (5)
unnamed: IC1.28 (PC5(ADC5/SCL/PCINT13)), JP2.5, R6.2
unnamed: IC1.24 (PC1(ADC1/PCINT9)), JP3.2, R5.2
unnamed: IC1.7 (PB6(XTAL1/TOSC1/PCINT6)), R5.1
unnamed: LED1.A, R1.2
unnamed: IC1.12 (PB0(ICP1/CLKO/PCINT0)), IC2.14 (NSEL), R4.1
unnamed: IC1.30 (PD0(RXD/PCINT16)), JP14.1
unnamed: IC1.32 (PD2(INT0/PCINT18)), IC2.2 (NIRQ)
unnamed: IC2.8 (ANT), JP5.1
unnamed: IC1.2 (PD4(T0/XCK/PCINT20)), JP11.1, R9.1
unnamed: IC1.8 (PB7(XTAL2/TOSC2/PCINT7)), SJ2.1
unnamed: IC2.6 (NRES), SJ2.2
unnamed: IC1.25 (PC2(ADC2/PCINT10)), JP2.2
unnamed: IC1.31 (PD1(TXD/PCINT17)), JP8.1
unnamed: IC1.9 (PD5(T1/OC0B/PCINT21)), JP9.1
VCC: BAT.VCC1, BAT.VCC2, C1.1, IC1.4 (VCC), IC1.6 (VCC), IC1.18 (AVCC), IC2.3 (FSK/DATA/NFFS), IC2.9 (VDD), JP2.6, R4.2, R6.1, R7.1, R8.1, R9.2, SJ1.1

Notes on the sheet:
smarthomatic Generic Micro 2
Date: 10.12.2015
Rev 1.0
Copyright (c) Uwe Freese, www.smarthomatic.org

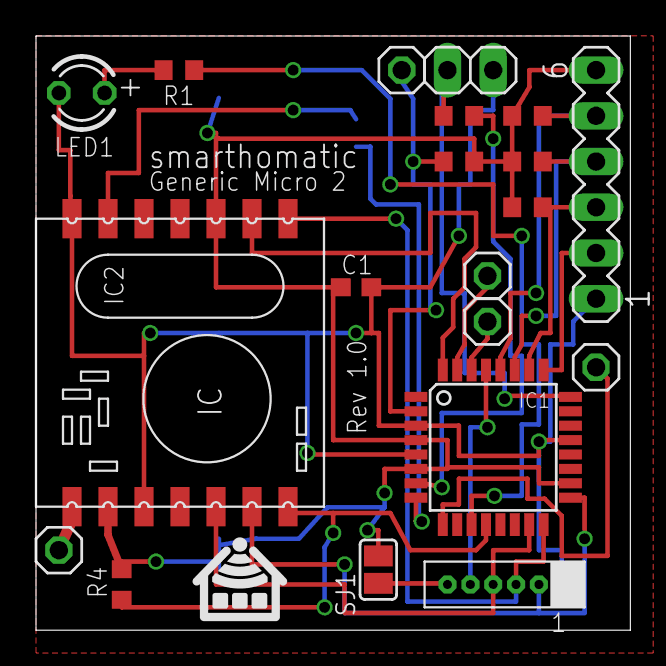
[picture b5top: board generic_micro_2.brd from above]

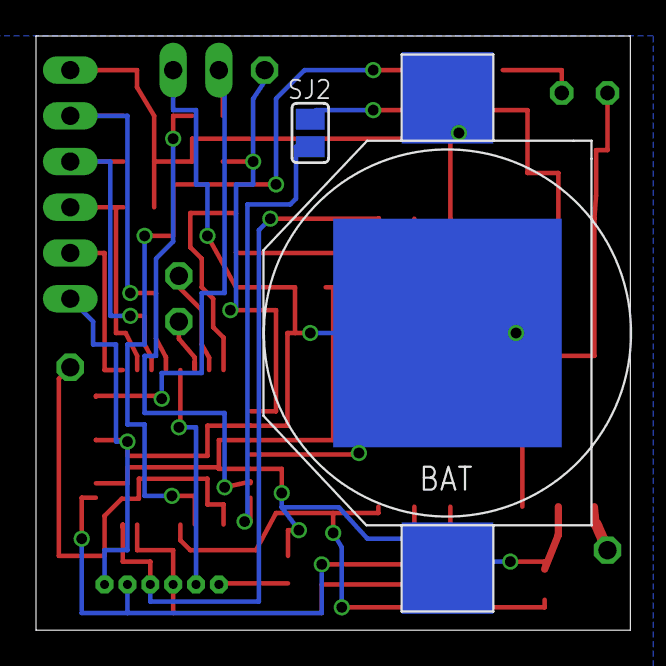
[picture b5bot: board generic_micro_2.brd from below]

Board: 2 copper layers, 33.0 x 33.0 mm, 22 parts (2 on the bottom side), 24 nets.
